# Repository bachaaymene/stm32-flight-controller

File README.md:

# STM32F405 Flight Controller

A 4-layer flight controller board for an F450 quadcopter frame, based on the STM32F405RGT6. Designed in KiCad 10 by [SparkLab DZ](https://sparklabdz.com).

## Features

| Block | Part | Notes |
|---|---|---|
| MCU | STM32F405RGT6 (LQFP64) | Cortex-M4F, 168 MHz, 1 MB Flash |
| IMU | LSM6DSO | SPI1, INT1 on PC4 |
| Barometer | LPS22HB | I2C1, address 0x5C |
| Motor outputs | 4x ESC | PC6 to PC9 on TIM3 (DShot capable) |
| 5V regulator | AP63205WU-7 | Synchronous buck, 3S LiPo input, 4.7 uH inductor |
| 3.3V regulator | TLV70233 | LDO from 5V |
| USB | USB Type-C 16P | PA11 / PA12 |
| Battery sense | 33k / 10k divider | PA0 (ADC) |

## Schematic

Full schematic as PDF: [post/flight_controller.pdf](post/flight_controller.pdf)

## PCB Layout

### Stackup

| Layer | Use |
|---|---|
| L1 | Signal + components |
| L2 | Solid GND plane |
| L3 | Power |
| L4 | Signal |

## Pin Map

| Function | Pin(s) |
|---|---|
| IMU SPI1 (CS / SCK / MISO / MOSI) | PA4 / PA5 / PA6 / PA7 |
| IMU interrupt (INT1) | PC4 |
| Baro I2C1 (SCL / SDA) | PB6 / PB7 |
| ESC 1 to 4 | PC6 / PC7 / PC8 / PC9 |
| USB D- / D+ | PA11 / PA12 |
| Battery voltage | PA0 |

Pin configuration in STM32CubeIDE:

## Repository Structure

```
stm32-flight-controller/
├── datasheets/                      Component datasheets
├── libs/                            Project symbols, footprints and 3D models
├── post/                            Schematic PDF and images
├── flight_controller.kicad_pro      KiCad project
├── flight_controller.kicad_sch      Schematic
├── flight_controller.kicad_pcb      PCB layout
├── flight_controller.csv            Bill of materials
├── fabrication-toolkit-options.json Fabrication Toolkit plugin settings
├── sym-lib-table                    Project symbol library table
├── fp-lib-table                     Project footprint library table
├── .gitattributes                   Git LFS settings
└── .gitignore
```

## Opening the Project

Requirements: **KiCad 10.0 or newer**. Older versions cannot open these files.

The repository uses Git LFS for large files, so install it before cloning:

```bash
git lfs install
git clone https://github.com/bachaaymene/stm32-flight-controller.git
```

Then open `flight_controller.kicad_pro` in KiCad.

All symbols, footprints and 3D models are stored in `libs/` with paths relative to the project (`${KIPRJMOD}`), so no external libraries are needed. If something appears missing, please open an issue.

## Manufacturing

The BOM is in `flight_controller.csv`.

Production files (Gerber, drill, BOM and CPL) for JLCPCB can be generated with the [Fabrication Toolkit](https://github.com/bennymeg/Fabrication-Toolkit) plugin. Install it from the KiCad Plugin and Content Manager, then run it from the PCB editor. The settings used for this board are saved in `fabrication-toolkit-options.json`.

## Status

- [x] Schematic
- [x] PCB layout
- [ ] Prototype fabrication
- [ ] Hardware bring-up
- [ ] Firmware

## License

This hardware design is released under the [CERN-OHL-S-2.0](LICENSE) license.

## Author

Aymene Bacha, [SparkLab DZ](https://sparklabdz.com)

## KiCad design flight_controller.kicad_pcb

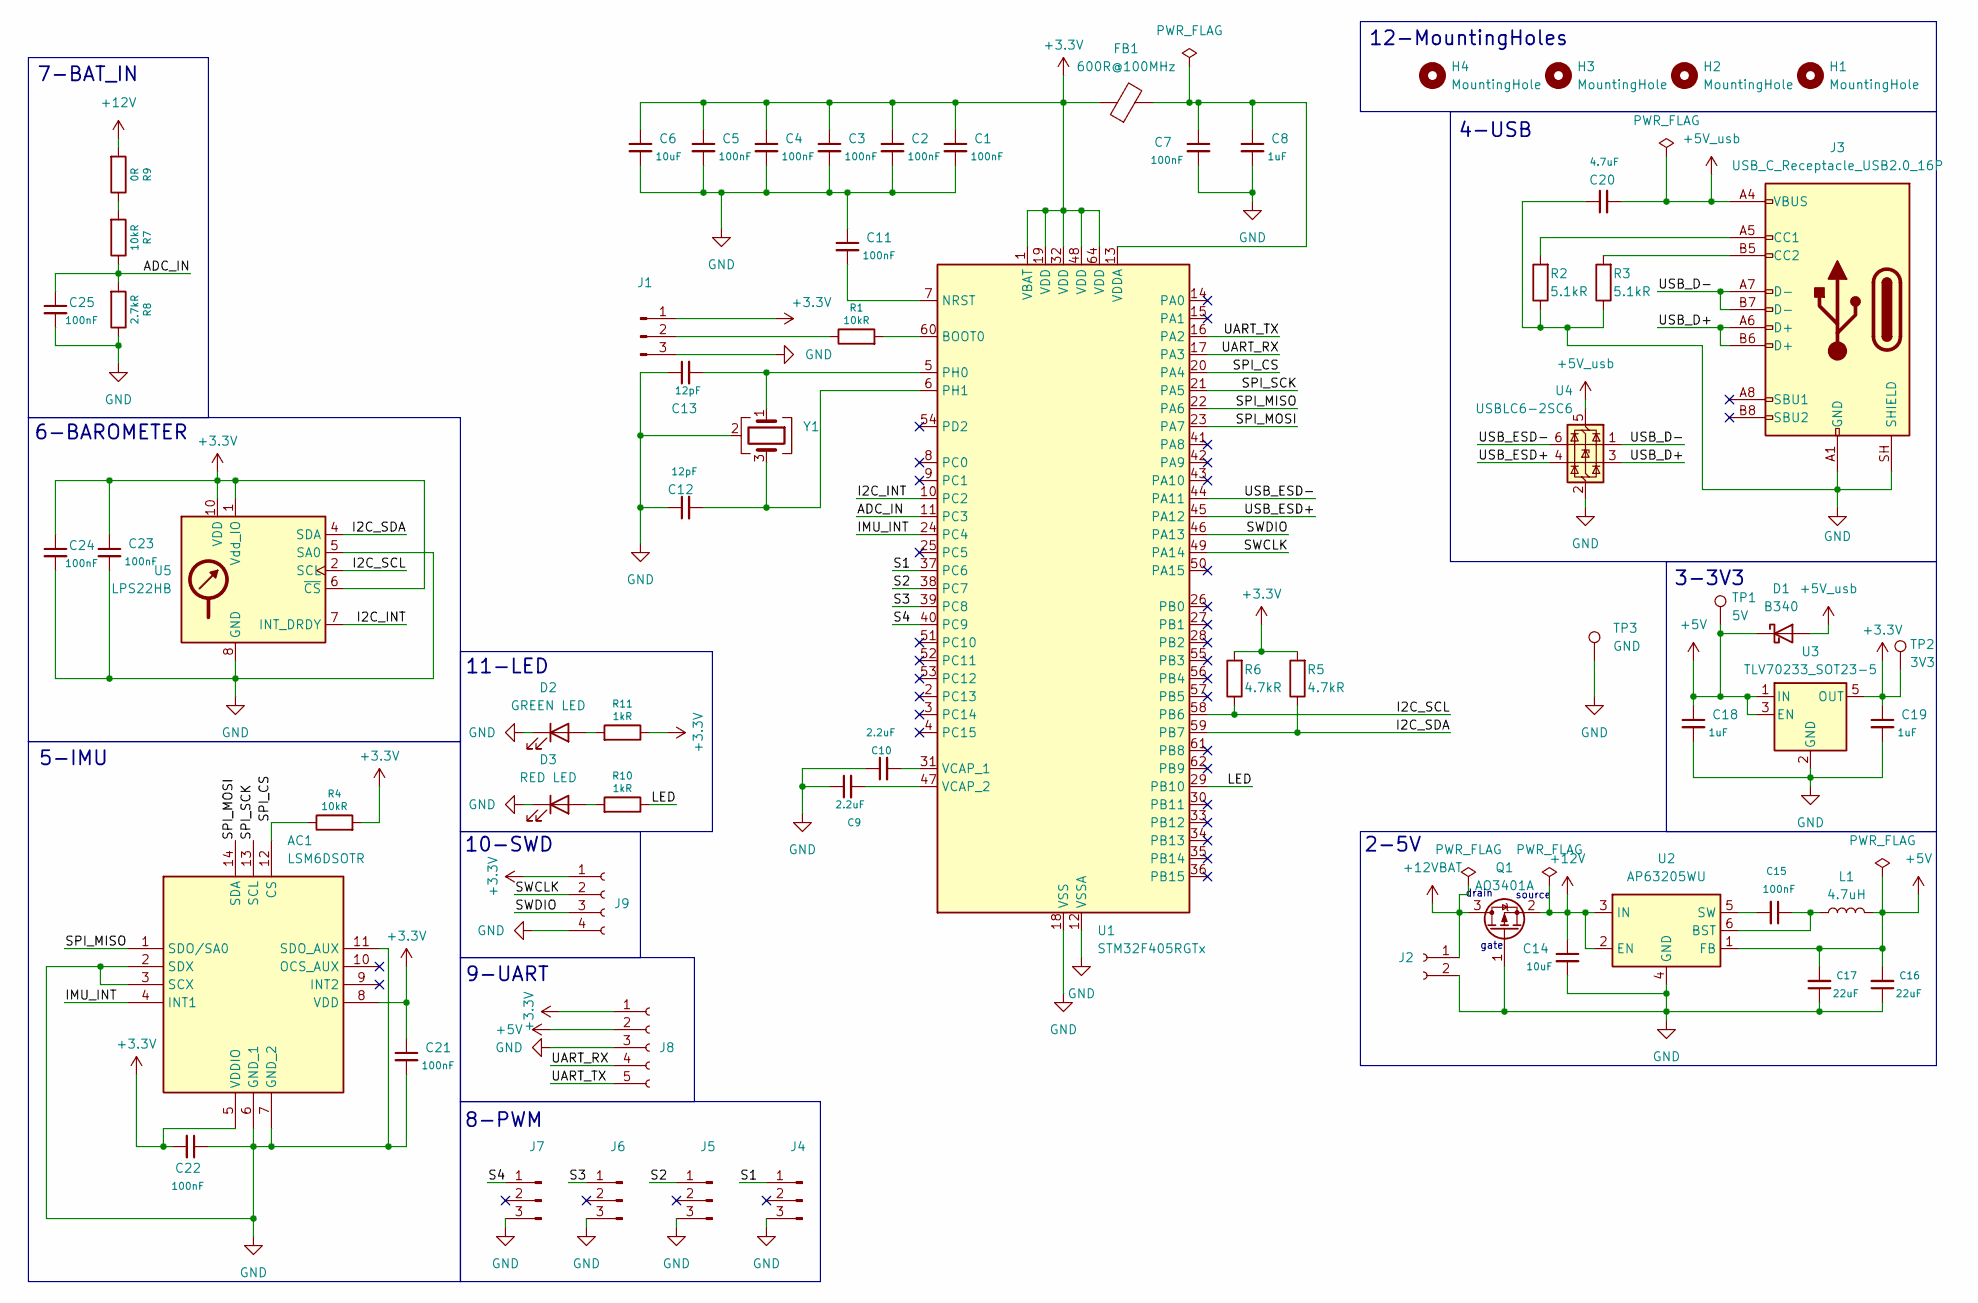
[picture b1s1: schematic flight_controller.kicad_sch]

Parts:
AC1: LSM6DSOTR; LGA-14_3x2.5mm_P0.5mm_LayoutBorder3x4y; Manufacturer_Part_Number LSM6DSOTR; Mouser Part Number 511-LSM6DSOTR
C1, C2, C3, C4, C5, C7, C11, C15, C21, C22, C23, C24, C25: 100nF; C_0402_1005Metric; LCSC C60474
C6: 10uF; C_0805_2012Metric; LCSC C77075
C8, C18, C19: 1uF; C_0603_1608Metric; LCSC C59782
C9, C10: 2.2uF; C_0805_2012Metric; LCSC C1731
C12, C13: 12pF; C_0402_1005Metric; LCSC C3899757
C14: 10uF; C_0805_2012Metric; LCSC C386085
C16, C17: 22uF; C_1206_3216Metric; LCSC C7432785
C20: 4.7uF; C_0805_2012Metric; LCSC C1746
D1: B340; D_SMC; LCSC C388236
D2: GREEN LED; LED_0805_2012Metric; LCSC C84260
D3: RED LED; LED_0805_2012Metric; LCSC C2971979
FB1: 600R@100MHz; L_0805_2012Metric; LCSC C527966
H1, H2, H3, H4: MountingHole; MountingHole_3.7mm_Pad_Via
J1, J4, J5, J6, J7: Conn_01x03_Pin; PinHeader_1x03_P2.54mm_Vertical
J2: Conn_01x02_Socket; PinSocket_1x02_P2.54mm_Vertical
J3: USB_C_Receptacle_USB2.0_16P; USB_C_Receptacle_HRO_TYPE-C-31-M-12; LCSC C2988369
J8: Conn_01x05_Socket; PinSocket_1x05_P2.54mm_Vertical
J9: Conn_01x04_Socket; PinSocket_1x04_P2.54mm_Vertical
L1: 4.7uH; L_Sunlord_MWSA0503S; LCSC C5349683
Q1: AO3401A; SOT-23; LCSC C15127
R1, R4, R7: 10kR; R_0402_1005Metric; LCSC C60490
R2, R3: 5.1kR; R_0402_1005Metric; LCSC C105872
R5, R6: 4.7kR; R_0402_1005Metric; LCSC C105871
R8: 2.7kR; R_0402_1005Metric; LCSC C138017
R9: 0R; R_0402_1005Metric; LCSC C106231
R10, R11: 1kR; R_0402_1005Metric; LCSC C106235
TP1: 5V; TestPoint_Pad_D1.0mm
TP2: 3V3; TestPoint_Pad_D1.0mm
TP3: GND; TestPoint_Pad_D1.0mm
U1: STM32F405RGTx; LQFP-64_10x10mm_P0.5mm; LCSC C15742
U2: AP63205WU; TSOT-23-6; LCSC C15742
U3: TLV70233_SOT23-5; SOT-23-5; LCSC C26833
U4: USBLC6-2SC6; SOT-23-6; LCSC C2827654
U5: LPS22HB; ST_HLGA-10_2x2mm_P0.5mm_LayoutBorder3x2y; LCSC C94049
Y1: 8MHz Crystal_GND24; Crystal_SMD_3225-4Pin_3.2x2.5mm; LCSC C400090

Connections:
+3.3V: AC1.5 (VDDIO), AC1.8 (VDD), C1.1, C2.1, C3.1, C4.1, C5.1, C6.1, C19.1, C21.1, C22.2, C23.1, C24.1, FB1.1, J1.1, J8.1, J9.1, R4.2, R5.2, R6.2, R11.1, TP2.1, U1.1 (VBAT), U1.19 (VDD), U1.32 (VDD), U1.48 (VDD), U1.64 (VDD), U3.5 (OUT), U5.1 (Vdd_IO), U5.6 (~CS), U5.10 (VDD); also elsewhere on the board
+5V: C16.2, C17.2, C18.1, D1.1 (K), J8.2, L1.2, TP1.1, U2.1 (FB), U3.1 (IN), U3.3 (EN); also elsewhere on the board
+5V_usb: C20.2, D1.2 (A), J3.A4 (VBUS), J3.A9 (VBUS), J3.B4 (VBUS), J3.B9 (VBUS), U4.5 (VBUS)
+12V: C14.1, Q1.2 (S), R9.2, U2.2 (EN), U2.3 (IN)
+12VBAT: J2.1, Q1.3 (D)
/ADC_IN: C25.1, R7.1, R8.2, U1.11 (PC3)
/I2C_INT: U1.10 (PC2), U5.7 (INT_DRDY)
/I2C_SCL: R6.1, U1.58 (PB6), U5.2 (SCL)
/I2C_SDA: R5.1, U1.59 (PB7), U5.4 (SDA)
/IMU_INT: AC1.4 (INT1), U1.24 (PC4)
/LED: R10.1, U1.29 (PB10)
/S1: J4.1, U1.37 (PC6)
/S2: J5.1, U1.38 (PC7)
/S3: J6.1, U1.39 (PC8)
/S4: J7.1, U1.40 (PC9)
/SPI_CS: AC1.12 (CS), R4.1, U1.20 (PA4)
/SPI_MISO: AC1.1 (SDO/SA0), U1.22 (PA6)
/SPI_MOSI: AC1.14 (SDA), U1.23 (PA7)
/SPI_SCK: AC1.13 (SCL), U1.21 (PA5)
/SWCLK: J9.2, U1.49 (PA14)
/SWDIO: J9.3, U1.46 (PA13)
/UART_RX: J8.4, U1.17 (PA3)
/UART_TX: J8.5, U1.16 (PA2)
/USB_D+: J3.A6 (D+), J3.B6 (D+), U4.3 (I/O2)
/USB_D-: J3.A7 (D-), J3.B7 (D-), U4.1 (I/O1)
/USB_ESD+: U1.45 (PA12), U4.4 (I/O2)
/USB_ESD-: U1.44 (PA11), U4.6 (I/O1)
GND: AC1.2 (SDX), AC1.3 (SCX), AC1.6 (GND_1), AC1.7 (GND_2), AC1.11 (SDO_AUX), C1.2, C2.2, C3.2, C4.2, C5.2, C6.2, C7.2, C8.2, C9.1, C10.1, C11.1, C12.1, C13.1, C14.2, C16.1, C17.1, C18.2, C19.2, C20.1, C21.2, C22.1, C23.2, C24.2, C25.2, D2.1 (K), D3.1 (K), J1.3, J2.2, J3.A1 (GND), J3.A12 (GND), J3.B1 (GND), J3.B12 (GND), J3.SH (SHIELD), J4.3, J5.3, J6.3, J7.3, J8.3, J9.4, Q1.1 (G), R2.1, R3.1, R8.1, TP3.1, U1.12 (VSSA), U1.18 (VSS), U1.63 (VSS), U2.4 (GND), U3.2 (GND), U4.2 (GND), U5.3 (GND), U5.5 (SA0), U5.8 (GND), U5.9 (GND), Y1.2 (G), Y1.4 (G); also elsewhere on the board
unnamed: D2.2 (A), R11.2
unnamed: D3.2 (A), R10.2
unnamed: J1.2, R1.1
unnamed: J3.A5 (CC1), R2.2
unnamed: J3.B5 (CC2), R3.2
unnamed: R7.2, R9.1
unnamed: R1.2, U1.60 (BOOT0)
unnamed: C11.2, U1.7 (NRST)
unnamed: C13.2, U1.5 (PH0), Y1.1
unnamed: C12.2, U1.6 (PH1), Y1.3
unnamed: C10.2, U1.31 (VCAP_1)
unnamed: C9.2, U1.47 (VCAP_2)
unnamed: C7.1, C8.1, FB1.2, U1.13 (VDDA)
unnamed: C15.1, L1.1, U2.6 (BST)
unnamed: C15.2, U2.5 (SW)

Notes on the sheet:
source
2-5V
gate
3-3V3
4-USB
7-BAT_IN
6-BAROMETER
12-MountingHoles
10-SWD
5-IMU
8-PWM
drain
9-UART
11-LED

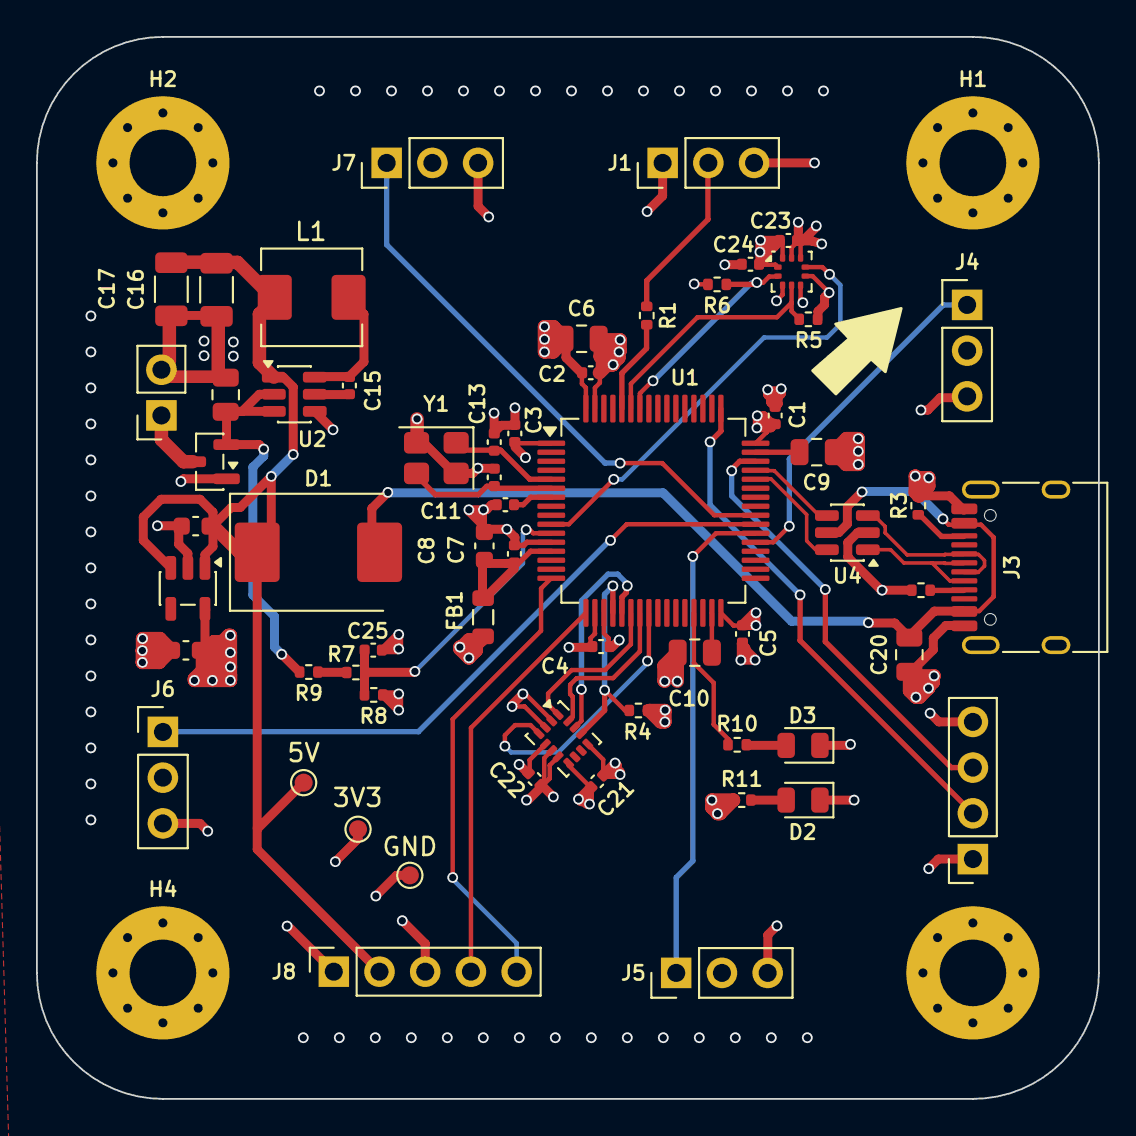
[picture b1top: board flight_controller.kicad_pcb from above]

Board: 4 copper layers, 59.0 x 59.0 mm, 65 parts (0 on the bottom side), 43 nets.

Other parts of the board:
3V3: 3V3; TestPoint_Pad_D1.0mm
5V: 5V; TestPoint_Pad_D1.0mm
GND: GND; TestPoint_Pad_D1.0mm

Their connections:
+3.3V: 3V3.1 (1_1); also elsewhere on the board
+5V: 5V.1 (1_1); also elsewhere on the board
GND: GND.1 (1_1); also elsewhere on the board
